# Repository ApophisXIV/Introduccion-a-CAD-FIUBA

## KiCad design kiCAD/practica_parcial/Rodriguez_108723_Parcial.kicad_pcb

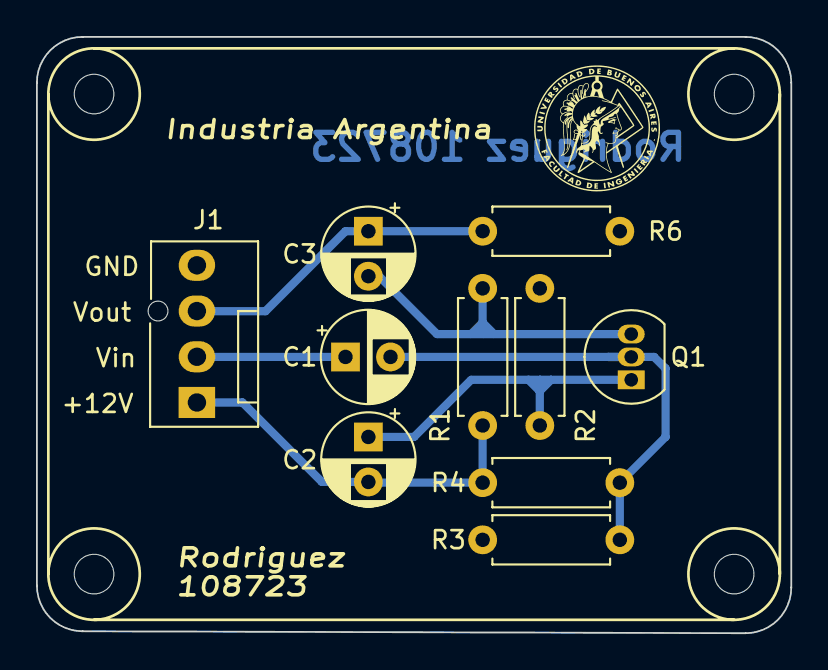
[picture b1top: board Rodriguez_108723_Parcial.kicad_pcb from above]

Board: 2 copper layers, 41.9 x 33.1 mm, 14 parts (0 on the bottom side), 7 nets.

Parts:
C1, C3: 1u; CP_Radial_D5.0mm_P2.50mm
C2: 1m; CP_Radial_D5.0mm_P2.50mm
H1, H2, H3, H4: MountingHole; MountingHole_2.2mm_M2
J1: Molex; FanPinHeader_1x04_P2.54mm_Vertical
Q1: 2N3904; TO-92_Inline
R1: 600; R_Axial_DIN0207_L6.3mm_D2.5mm_P7.62mm_Horizontal
R2: 400; R_Axial_DIN0207_L6.3mm_D2.5mm_P7.62mm_Horizontal
R3: 1k; R_Axial_DIN0207_L6.3mm_D2.5mm_P7.62mm_Horizontal
R4: 3k; R_Axial_DIN0207_L6.3mm_D2.5mm_P7.62mm_Horizontal
R6: 100; R_Axial_DIN0207_L6.3mm_D2.5mm_P7.62mm_Horizontal

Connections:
+12V: C2.2, J1.1, R1.1, R4.1
/Signal_in: C1.1, J1.2
/Vb: C1.2, Q1.2 (B), R3.1, R4.2
/Vc: C3.2, Q1.3 (C), R1.2
/Ve: C2.1, Q1.1 (E), R2.1
GND: J1.4, R2.2, R3.2, R6.2
Vout: C3.1, J1.3, R6.1

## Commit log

2023-08-26 First commit. Draw 1 to 7
2023-08-29 Add draw 9
2023-09-10 Practica OpenSCAD
2023-09-10 Version alternativa estufa
2023-09-15 OpenSCAD exercises
2023-09-15 OpenSCAD practice exercise [WIP]
2023-09-15 LibreCAD practice exercise
2023-09-17 Tech draw
2023-09-17 Update librecad files
2023-09-19 Design made. Added some documentation images
2023-09-24 Openscad practice complete
2023-10-03 Create several IC package
2023-10-03 Add some package datasheet
2023-10-10 Some practice before the midterm exam
2023-10-10 More changes
2023-10-10 Chuck wrench
2023-10-11 OpenSCAD done!!
2023-10-11 Some explanation
2023-10-11 Respuestas teoricas del parcial
2023-12-01 Parcial 1
2023-12-01 Parcial 2
